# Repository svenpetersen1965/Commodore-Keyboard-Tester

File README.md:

# Commodore-Keyboard-Tester
This is a tester for Commodore matrix keyboards for the following compurters:
* C64
* VIC-20
* PET/CBM
* C16
* C128
* C128D
* SX-64

It can measure the resistance of every single key, which requires a multimeter and two 4mm lab cables.

# Case (3D printed)

The 3D printed case offers a better protection of the bottom side and looks a bit nicer, than the stand off solution. It works with all released versions (100mm x
70mm PCB). 

Recommended screws are 4 each of C2.9 x 6.5 (self cutting, DIN 7981). The drill diameter is 2.5mm.

In case it is desired to use 2mm lab jacks, a 3mm deeper case (Rev. 2) has been released.

# Rev. 2
Rev. 2 is mainly a nicer looking silkscreen, than Rev. 1. Technically, this version is not any upgrade. 

# Info about rejuvenation keyboard rubber
As I said in the documentation, one reason for bad keys is the oil that is sweating from the conductive rubbers over the decades. This can be removed by soaking the rubbers in a mild caustic solution for at least 24hours.

Jeff Birt did some great research on this topic, which cou can find here:

<a href="https://youtu.be/n9gGz2n-sBU">Hey Birt! (Youtube): Resistance is futile Rejuvenating vintage computer keyboard key contacts</a>

Instead of ammonia, I am using a lye (NaOH) solution and I wrote somethng about it on my website:

<a href="http://tech.guitarsite.de/conductive_rubber.html">Rejuvenating The Conductive Rubber In a (Commodore) Keyboard</a>

After treating the keyboard rubbers, it might make sense to measure their resistance before installing them in the keyboard again. I found Jeff Birt's ficture quite nice for doing so. 

https://github.com/Jeff-Birt/C64_C128_Amiga_Mitsumi_Key_Tester

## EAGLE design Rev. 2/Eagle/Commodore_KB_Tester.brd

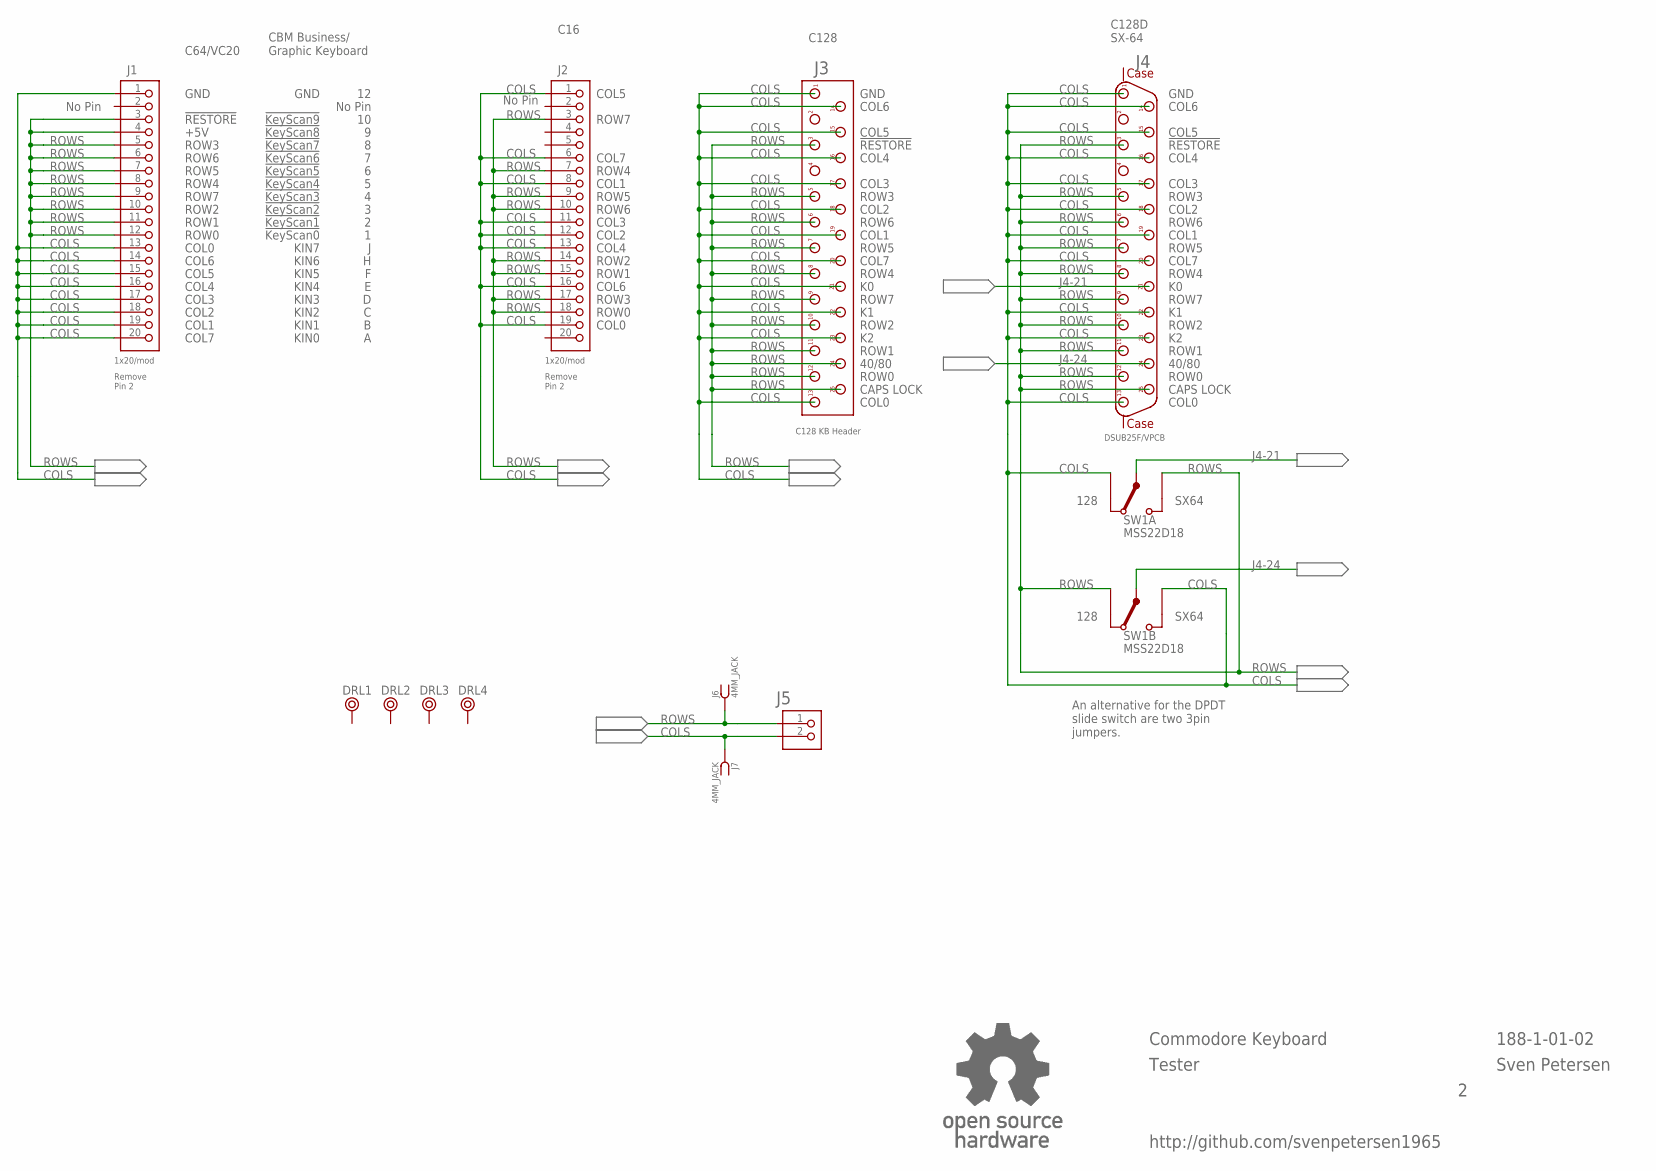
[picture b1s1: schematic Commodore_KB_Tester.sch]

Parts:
DRL1, DRL2, DRL3, DRL4: BOHR3,5
J1, J2: 1x20/mod; 1X20
J3: C128 KB Header; C128KB_HEADER
J4: DSUB25F/VPCB; DS25F-V
J5: PINHD-1X2; 1X02
J6, J7: 4MM_JACK; JACK4MM
SW1: MSS22D18; DPDT_9MM
U$12: OPEN_SOURCE_HW; OPENHW

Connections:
COLS: J1.1, J1.13, J1.14, J1.15, J1.16, J1.17, J1.18, J1.19, J1.20, J2.1, J2.6, J2.8, J2.11, J2.12, J2.13, J2.16, J2.19, J3.1, J3.13, J3.14, J3.15, J3.16, J3.17, J3.18, J3.19, J3.20, J3.21, J3.22, J3.23, J4.1, J4.13, J4.14, J4.15, J4.16, J4.17, J4.18, J4.19, J4.20, J4.22, J4.23, J5.2, J7.1, J7.1A, SW1.3 (DWN), SW1.6 (UP)
J4-21: J4.21, SW1.2 (COM)
J4-24: J4.24, SW1.5 (COM)
ROWS: J1.3, J1.4, J1.5, J1.6, J1.7, J1.8, J1.9, J1.10, J1.11, J1.12, J2.3, J2.7, J2.9, J2.10, J2.14, J2.15, J2.17, J2.18, J3.3, J3.5, J3.6, J3.7, J3.8, J3.9, J3.10, J3.11, J3.12, J3.24, J3.25, J4.3, J4.5, J4.6, J4.7, J4.8, J4.9, J4.10, J4.11, J4.12, J4.25, J5.1, J6.1, J6.1A, SW1.1 (UP), SW1.4 (DWN)

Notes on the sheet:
GND
!RESTORE
+5V
ROW3
ROW6
ROW5
ROW4
ROW7
ROW2
ROW1
ROW0
COL0
COL6
COL5
COL4
COL3
COL2
COL1
COL7
C64/VC20
No Pin
!KeyScan0
!KeyScan1
!KeyScan2
!KeyScan3
!KeyScan4
!KeyScan5
!KeyScan6
!KeyScan7
!KeyScan8
!KeyScan9
KIN0
KIN1
KIN2
KIN3
KIN4
KIN5
KIN6
KIN7
CBM Business/ Graphic Keyboard

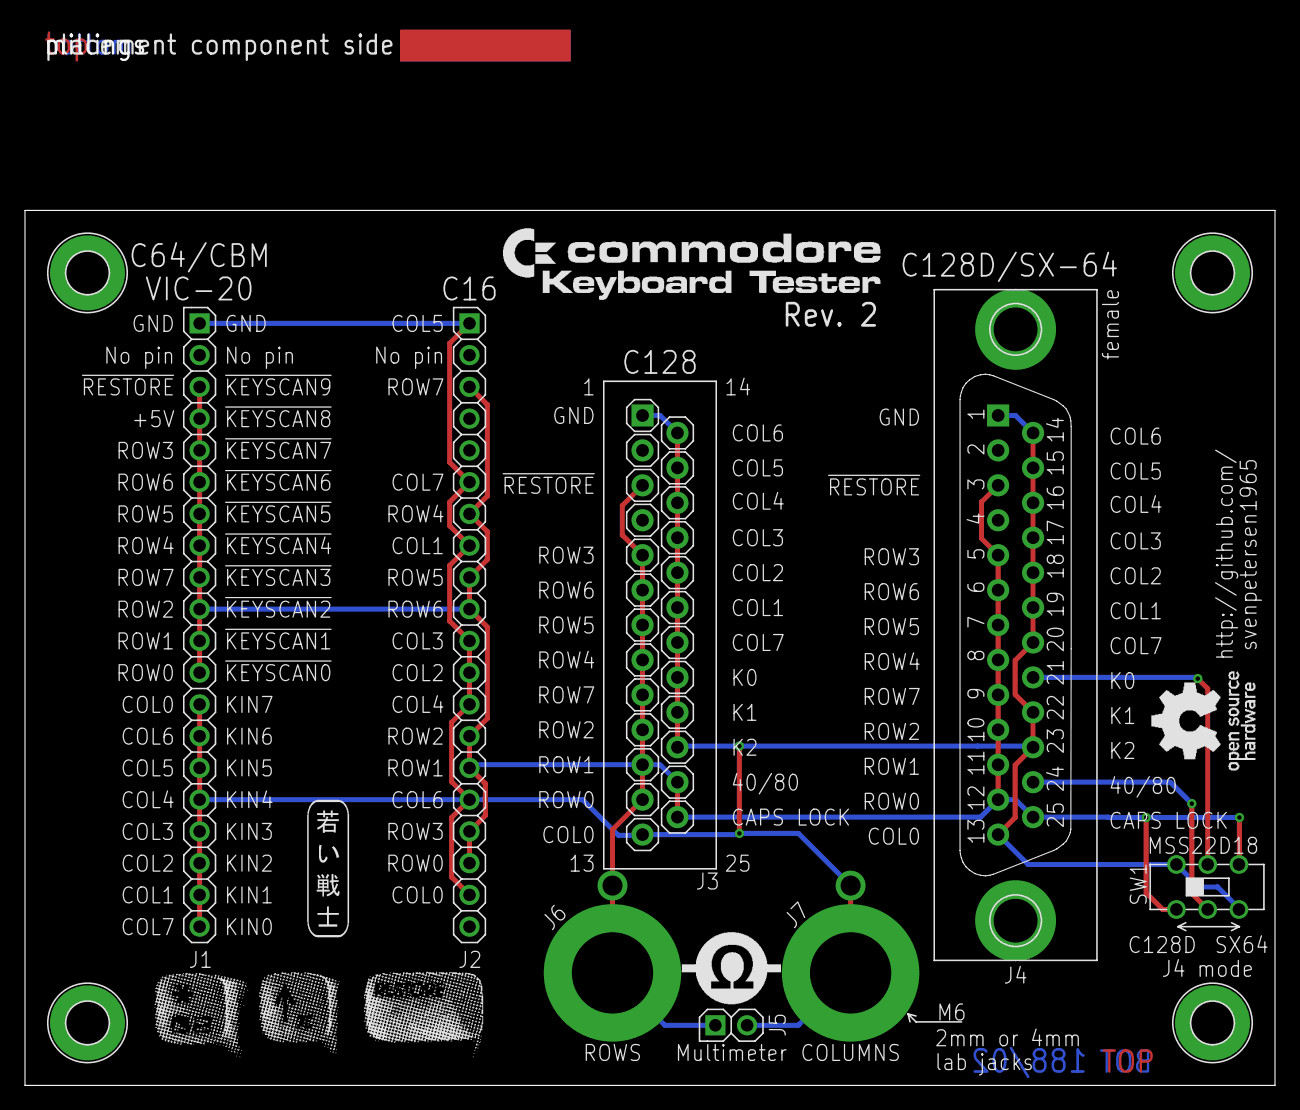
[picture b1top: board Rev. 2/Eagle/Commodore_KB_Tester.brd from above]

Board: 2 copper layers, 100.0 x 70.0 mm, 19 parts (0 on the bottom side), 4 nets.

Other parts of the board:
U$13: C64_KEYS
U$14: 2LAYER
U$15: PCB-TITLE/
U$16: COMMODORE_KB
U$21: SVEN_TAG
U$22: OHMMETER

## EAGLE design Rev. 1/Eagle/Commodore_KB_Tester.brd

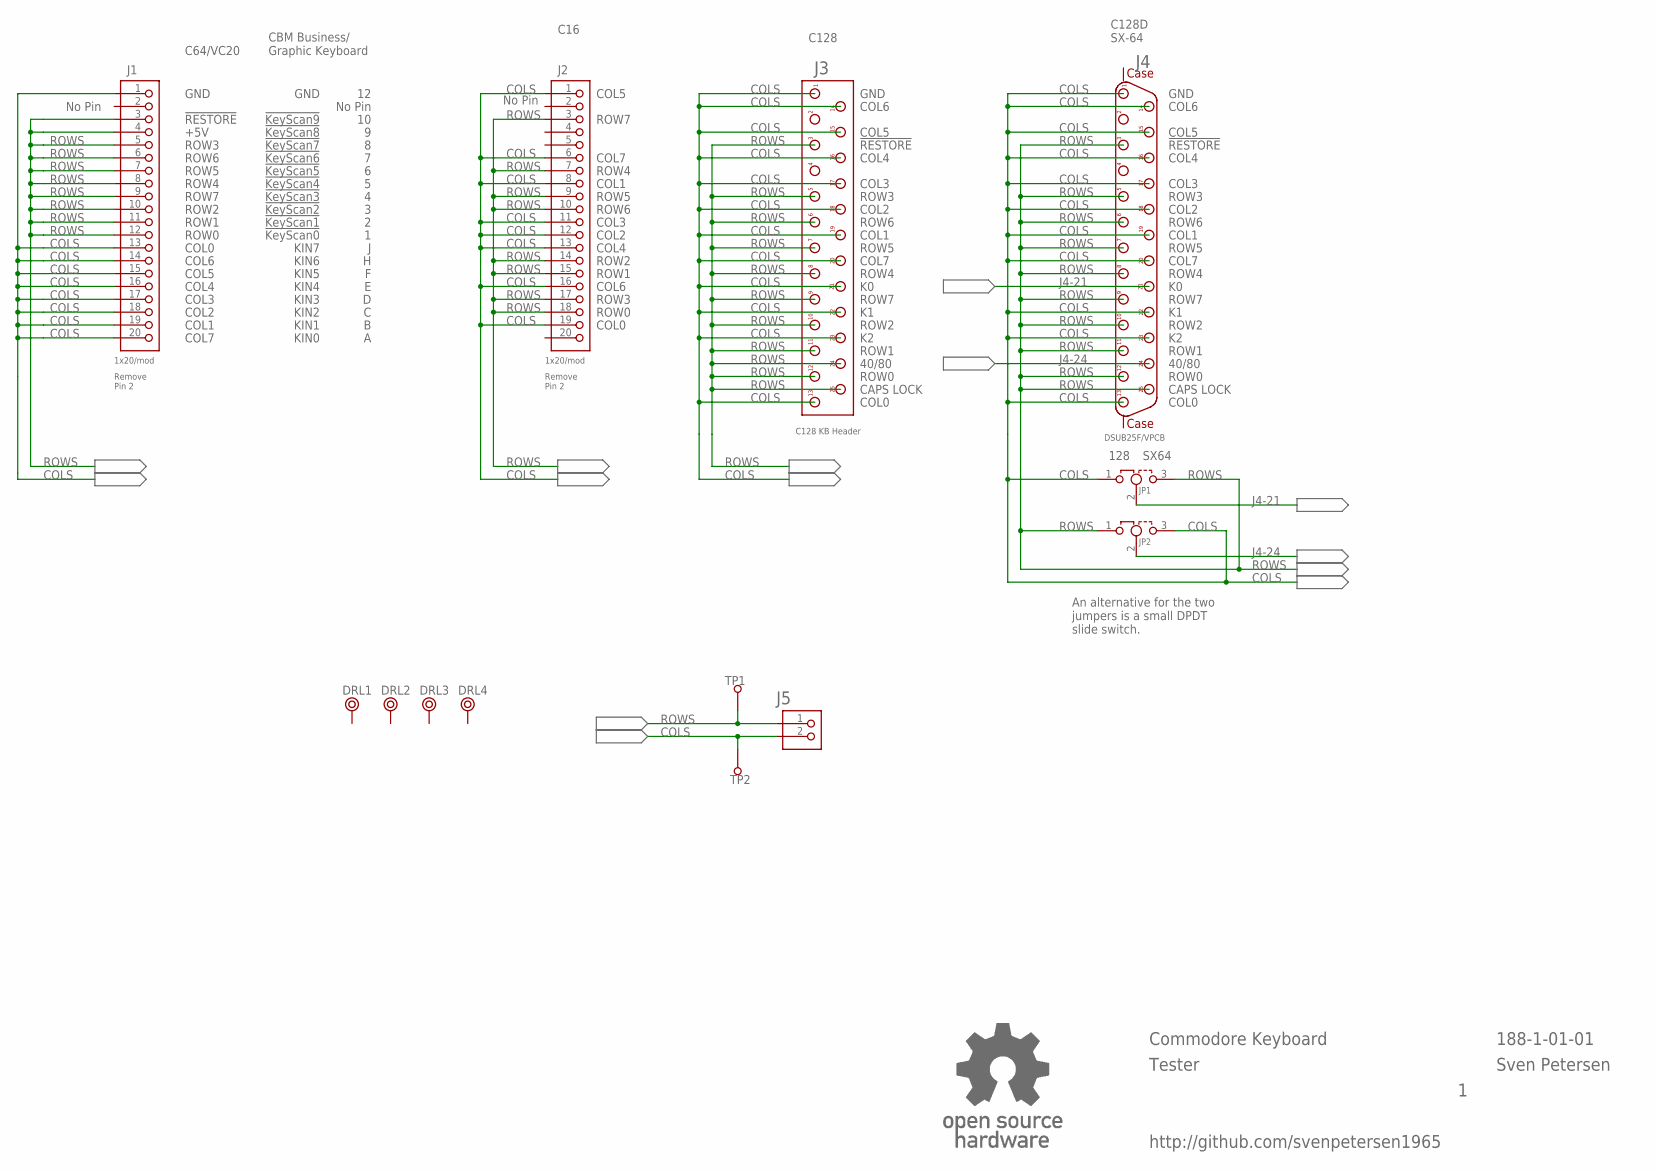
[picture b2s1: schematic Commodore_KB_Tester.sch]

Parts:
DRL1, DRL2, DRL3, DRL4: BOHR3,5
J1, J2: 1x20/mod; 1X20
J3: C128 KB Header; C128KB_HEADER
J4: DSUB25F/VPCB; DS25F-V
J5: PINHD-1X2; 1X02
JP1, JP2: DJUMPER; 1X03
TP1, TP2: 1,3/2,0
U$12: OPEN_SOURCE_HW; OPENHW

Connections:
COLS: J1.1, J1.13, J1.14, J1.15, J1.16, J1.17, J1.18, J1.19, J1.20, J2.1, J2.6, J2.8, J2.11, J2.12, J2.13, J2.16, J2.19, J3.1, J3.13, J3.14, J3.15, J3.16, J3.17, J3.18, J3.19, J3.20, J3.21, J3.22, J3.23, J4.1, J4.13, J4.14, J4.15, J4.16, J4.17, J4.18, J4.19, J4.20, J4.22, J4.23, J5.2, JP1.1, JP2.3, TP2.1
J4-21: J4.21, JP1.2
J4-24: J4.24, JP2.2
ROWS: J1.3, J1.4, J1.5, J1.6, J1.7, J1.8, J1.9, J1.10, J1.11, J1.12, J2.3, J2.7, J2.9, J2.10, J2.14, J2.15, J2.17, J2.18, J3.3, J3.5, J3.6, J3.7, J3.8, J3.9, J3.10, J3.11, J3.12, J3.24, J3.25, J4.3, J4.5, J4.6, J4.7, J4.8, J4.9, J4.10, J4.11, J4.12, J4.25, J5.1, JP1.3, JP2.1, TP1.1

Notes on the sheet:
GND
!RESTORE
+5V
ROW3
ROW6
ROW5
ROW4
ROW7
ROW2
ROW1
ROW0
COL0
COL6
COL5
COL4
COL3
COL2
COL1
COL7
C64/VC20
No Pin
!KeyScan0
!KeyScan1
!KeyScan2
!KeyScan3
!KeyScan4
!KeyScan5
!KeyScan6
!KeyScan7
!KeyScan8
!KeyScan9
KIN0
KIN1
KIN2
KIN3
KIN4
KIN5
KIN6
KIN7
CBM Business/ Graphic Keyboard

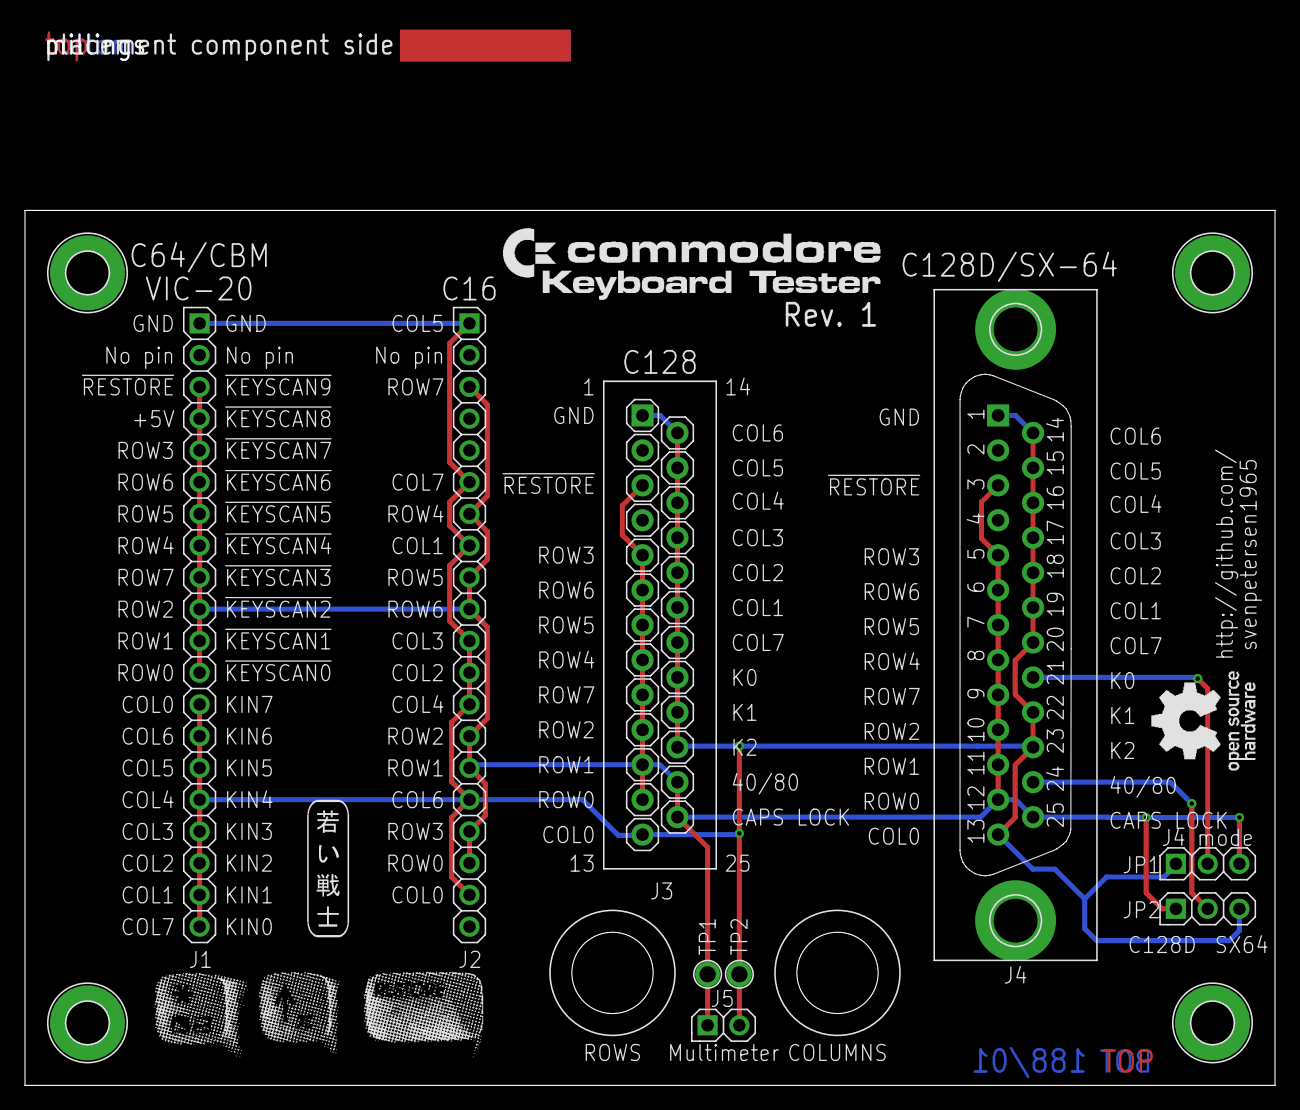
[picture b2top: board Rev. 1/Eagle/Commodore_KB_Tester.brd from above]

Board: 2 copper layers, 100.0 x 70.0 mm, 19 parts (0 on the bottom side), 4 nets.

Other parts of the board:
U$13: C64_KEYS
U$14: 2LAYER
U$15: PCB-TITLE/
U$16: COMMODORE_KB
U$21: SVEN_TAG

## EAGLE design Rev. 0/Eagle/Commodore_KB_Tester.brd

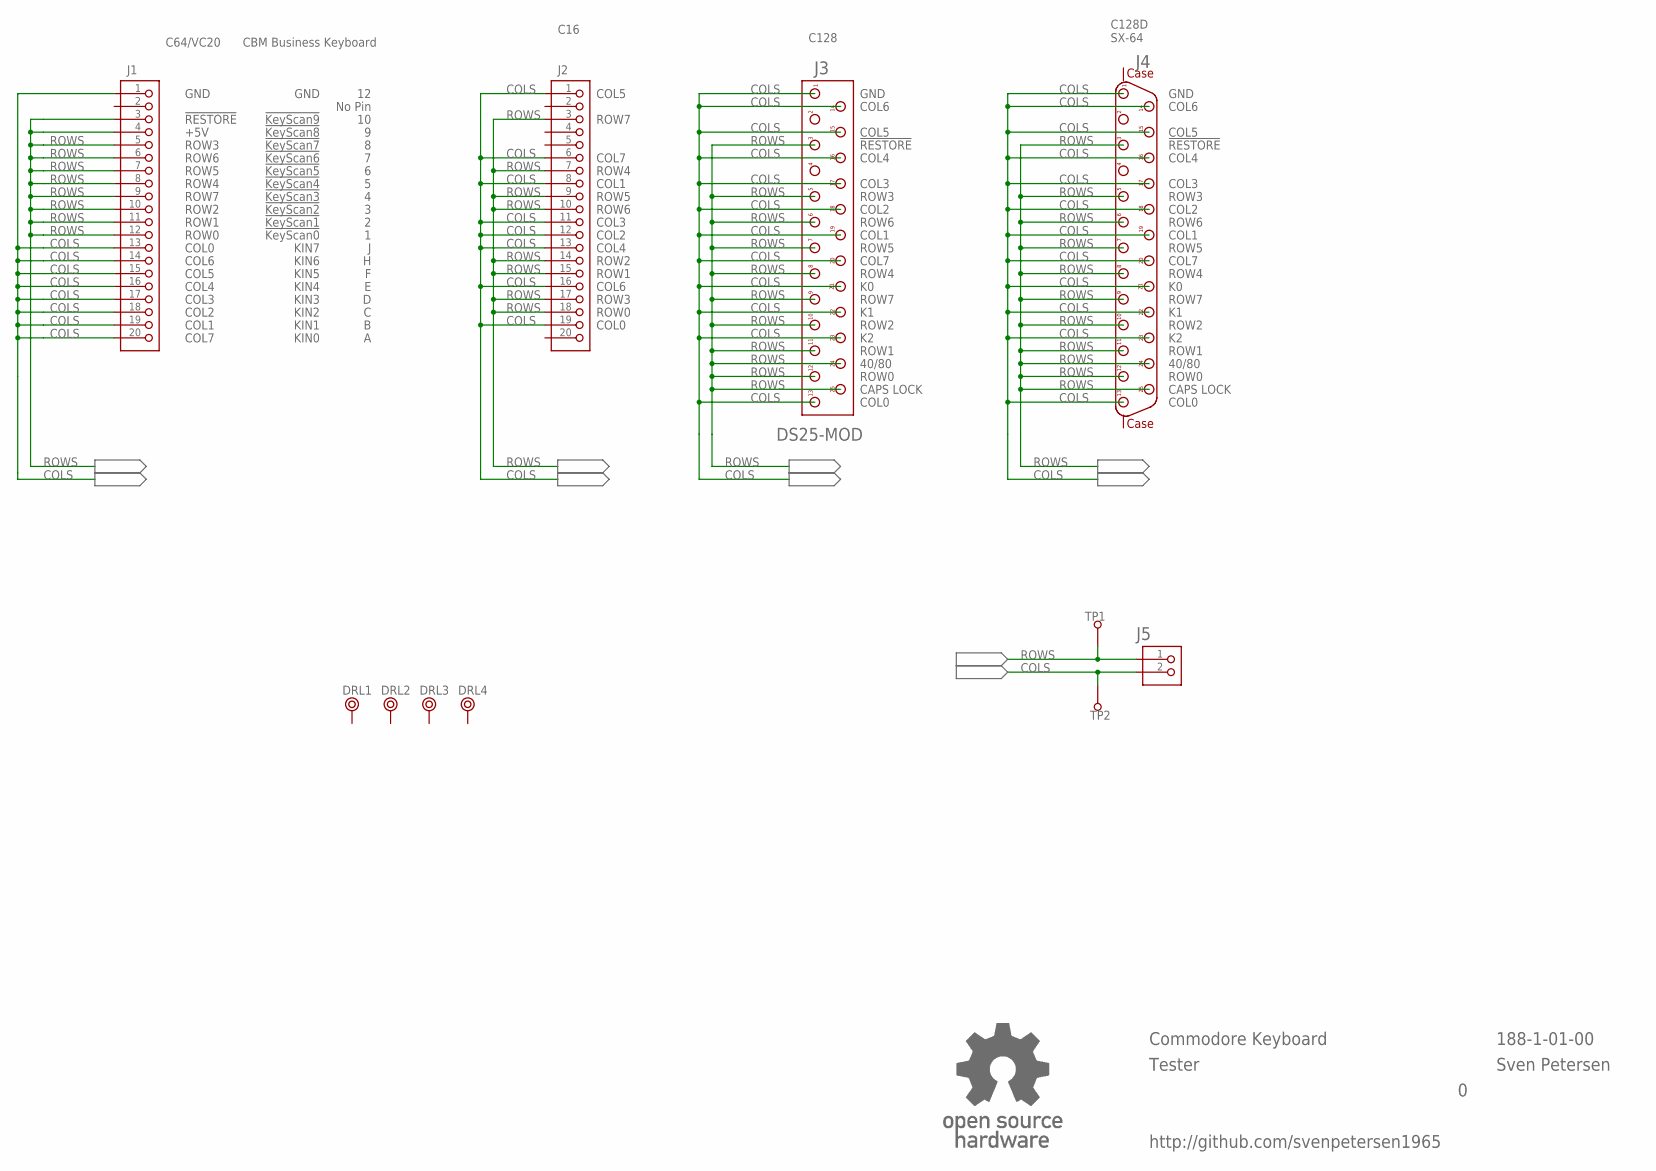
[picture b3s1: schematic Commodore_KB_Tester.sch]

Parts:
DRL1, DRL2, DRL3, DRL4: BOHR3,5
J1, J2: PINHD-1X20; 1X20
J3: DS25-MOD; C128KB_HEADER
J4: DS25F-V-CL; DS25F-V
J5: PINHD-1X2; 1X02
TP1, TP2: 1,3/2,0
U$12: OPEN_SOURCE_HW; OPENHW

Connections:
COLS: J1.1, J1.13, J1.14, J1.15, J1.16, J1.17, J1.18, J1.19, J1.20, J2.1, J2.6, J2.8, J2.11, J2.12, J2.13, J2.16, J2.19, J3.1, J3.13, J3.14, J3.15, J3.16, J3.17, J3.18, J3.19, J3.20, J3.21, J3.22, J3.23, J4.1, J4.13, J4.14, J4.15, J4.16, J4.17, J4.18, J4.19, J4.20, J4.21, J4.22, J4.23, J5.2, TP2.1
ROWS: J1.3, J1.4, J1.5, J1.6, J1.7, J1.8, J1.9, J1.10, J1.11, J1.12, J2.3, J2.7, J2.9, J2.10, J2.14, J2.15, J2.17, J2.18, J3.3, J3.5, J3.6, J3.7, J3.8, J3.9, J3.10, J3.11, J3.12, J3.24, J3.25, J4.3, J4.5, J4.6, J4.7, J4.8, J4.9, J4.10, J4.11, J4.12, J4.24, J4.25, J5.1, TP1.1

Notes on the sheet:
GND
!RESTORE
+5V
ROW3
ROW6
ROW5
ROW4
ROW7
ROW2
ROW1
ROW0
COL0
COL6
COL5
COL4
COL3
COL2
COL1
COL7
C64/VC20
No Pin
!KeyScan0
!KeyScan1
!KeyScan2
!KeyScan3
!KeyScan4
!KeyScan5
!KeyScan6
!KeyScan7
!KeyScan8
!KeyScan9
KIN0
KIN1
KIN2
KIN3
KIN4
KIN5
KIN6
KIN7
CBM Business Keyboard

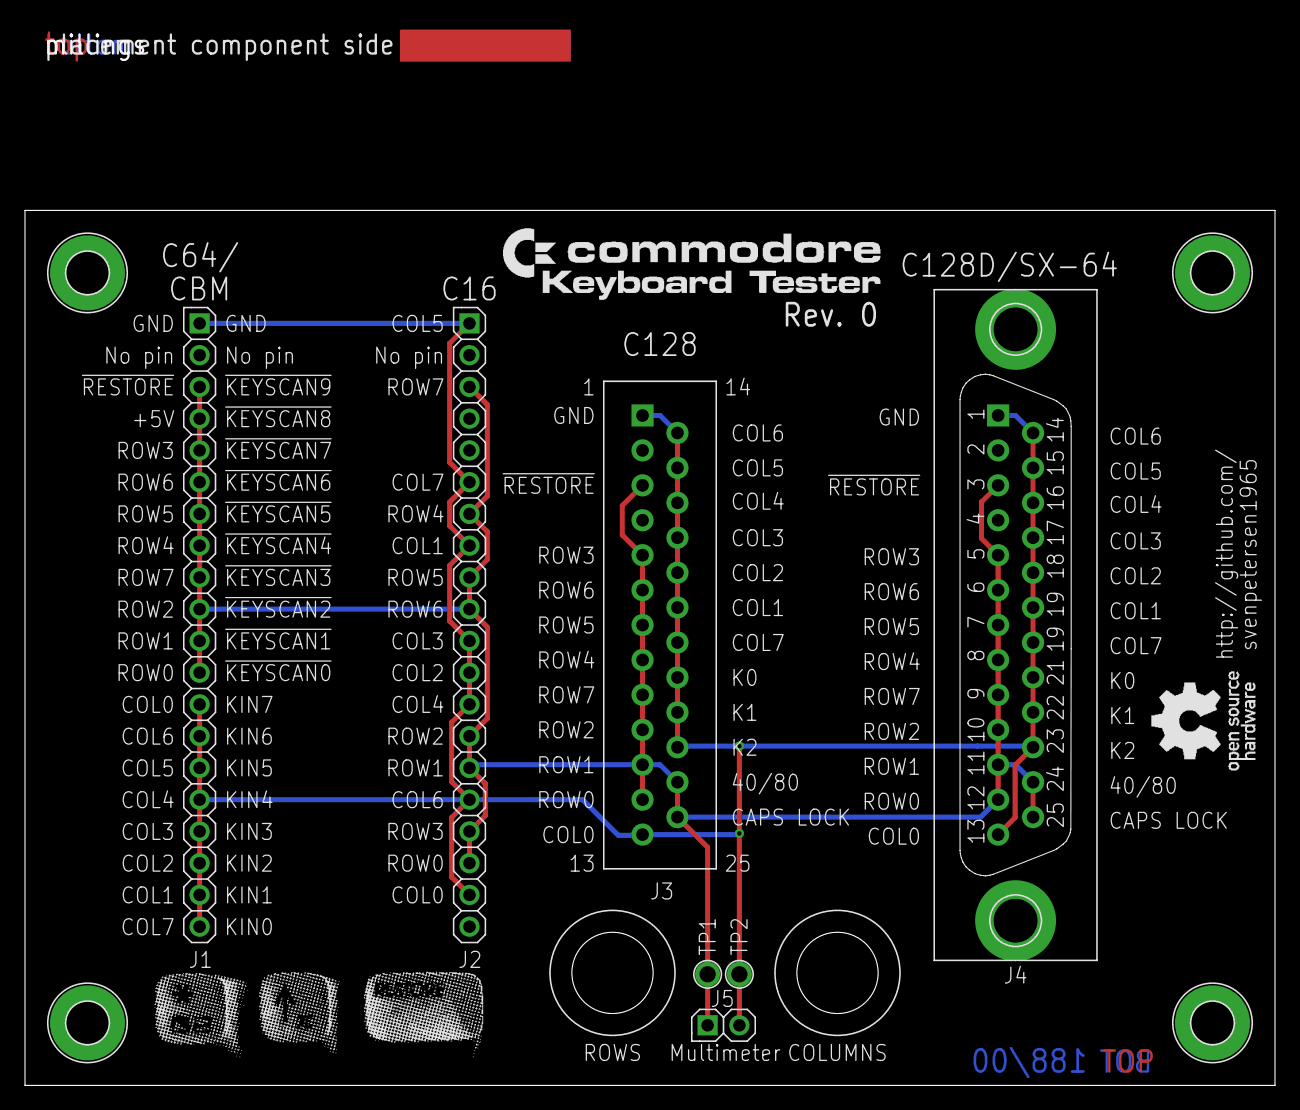
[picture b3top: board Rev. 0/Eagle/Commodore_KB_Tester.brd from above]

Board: 2 copper layers, 100.0 x 70.0 mm, 16 parts (0 on the bottom side), 2 nets.

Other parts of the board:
U$13: C64_KEYS
U$14: 2LAYER
U$15: PCB-TITLE/
U$16: COMMODORE_KB

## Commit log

2022-08-17 initial upload
2023-05-28 Rev. 2 released
2024-05-28 README.md aktualisieren
